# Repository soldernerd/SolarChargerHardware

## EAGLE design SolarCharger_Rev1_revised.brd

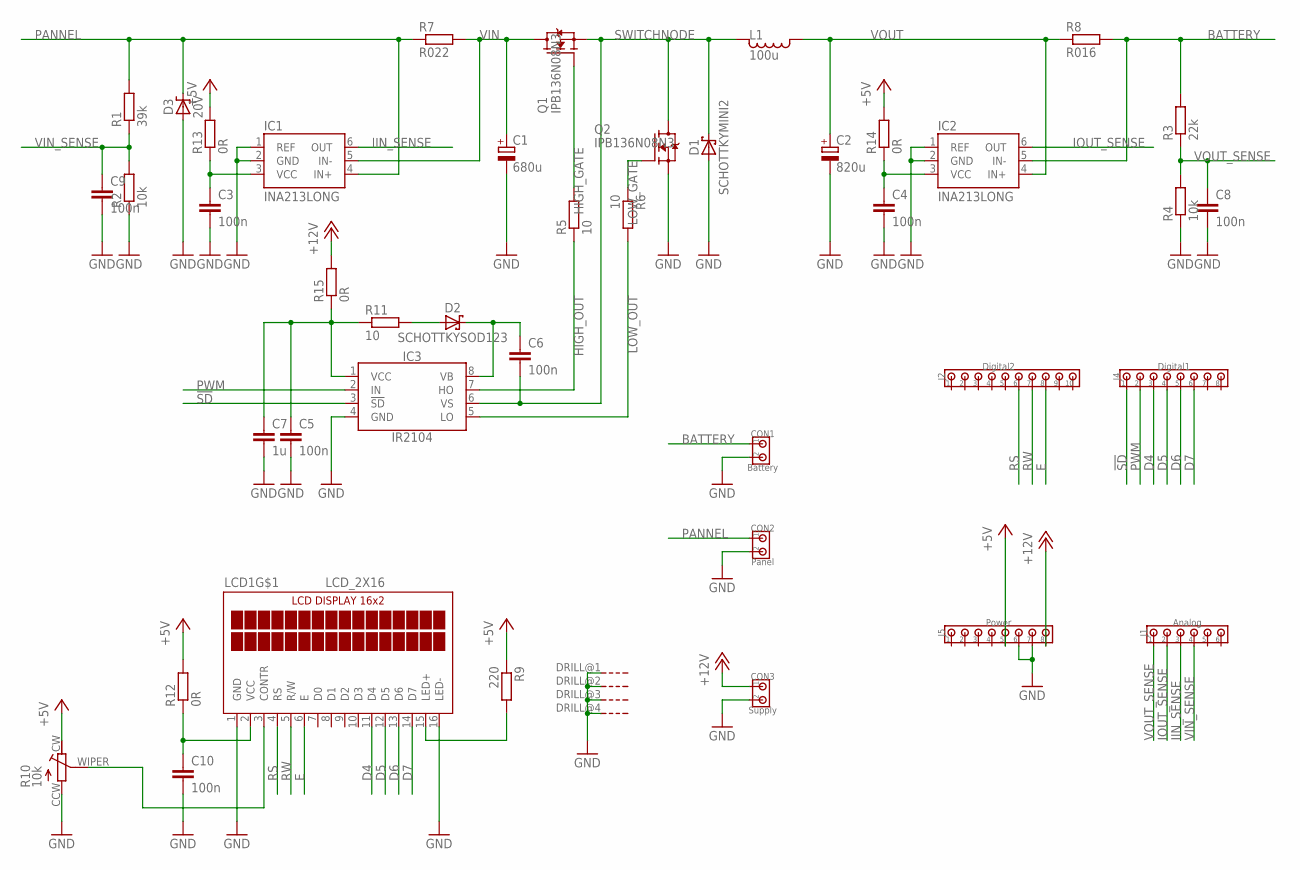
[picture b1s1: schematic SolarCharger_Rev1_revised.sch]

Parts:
C1: 680u; 10MM
C2: 820u; 10MM
C3, C4, C5, C6, C8, C9, C10: 100n; C0805
C7: 1u; C0805
CON1: Battery; 200MIL_2X
CON2: Panel; 200MIL_2X
CON3: Supply; 200MIL_2X
D1: SCHOTTKYMINI2; MINI2-F3-B
D2: SCHOTTKYSOD123; SOD123
D3: 20V; SMC
IC1, IC2: INA213LONG; SC70-6_LONG
IC3: IR2104; SOIC8
J1: Analog; 100MIL_6X_ROUND
J2: Digital2; 100MIL_10X_ROUND
J4: Digital1; 100MIL_8X_ROUND
J5: Power; 100MIL_8X_ROUND
L1: 100u; MSS1583
LCD1: LCD_2X16
Q1: IPB136N08N3; TO263-3
Q2: IPB136N08N3; TO263-3@1
R1: 39k; R0805
R2, R4: 10k; R0805
R3: 22k; R0805
R5, R6, R11: 10; R0805
R7: R022; 0612
R8: R016; 0612
R9: 220; R0805
R10: 10k; RTRIM3314G
R12, R13, R14, R15: 0R; R0805

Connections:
!SD!: IC3.3 (!SD!), J4.1
+5V: J5.5, R9.1, R10.CW, R12.2, R13.2, R14.2
+12V: CON3.1, J5.8, R15.2
BATTERY: CON1.1, IC2.5 (IN-), R3.2, R8.2
BOOT: C6.1, D2.C, IC3.8 (VB)
D4: J4.3, LCD1.11 (D4)
D5: J4.4, LCD1.12 (D5)
D6: J4.5, LCD1.13 (D6)
D7: J4.6, LCD1.14 (D7)
E: J2.8, LCD1.6 (E)
GND: C1.-, C2.-, C3.2, C4.2, C5.2, C7.2, C8.2, C9.2, C10.2, CON1.2, CON2.2, CON3.2, D1.A, D3.A, IC1.1 (REF), IC1.2 (GND), IC2.1 (REF), IC2.2 (GND), IC3.4 (GND), J5.6, J5.7, LCD1.1 (GND), LCD1.16 (LED-), LCD1.DRILL@1 (G), LCD1.DRILL@2 (G), LCD1.DRILL@3 (G), LCD1.DRILL@4 (G), Q2.3 (S), R2.1, R4.1, R10.CCW
HIGH_GATE: Q1.1 (G), R5.2
HIGH_OUT: IC3.7 (HO), R5.1
IIN_SENSE: IC1.6 (OUT), J1.3
IOUT_SENSE: IC2.6 (OUT), J1.2
LOW_GATE: Q2.1 (G), R6.1
LOW_OUT: IC3.5 (LO), R6.2
unnamed: C10.1, LCD1.2 (VCC), R12.1
unnamed: C3.1, IC1.3 (VCC), R13.1
unnamed: C4.1, IC2.3 (VCC), R14.1
unnamed: C5.1, C7.1, IC3.1 (VCC), R11.1, R15.1
unnamed: LCD1.15 (LED+), R9.2
unnamed: LCD1.3 (CONTR), R10.WIPER
unnamed: D2.A, R11.2
PANNEL: CON2.1, D3.C, IC1.4 (IN+), R1.2, R7.1
PWM: IC3.2 (IN), J4.2
RS: J2.6, LCD1.4 (RS)
RW: J2.7, LCD1.5 (R/W)
SWITCHNODE: C6.2, D1.C, IC3.6 (VS), L1.2, Q1.3 (S), Q2.TAB (D)
VIN: C1.+, IC1.5 (IN-), Q1.TAB (D), R7.2
VIN_SENSE: C9.1, J1.4, R1.1, R2.2
VOUT: C2.+, IC2.4 (IN+), L1.1, R8.1
VOUT_SENSE: C8.1, J1.1, R3.1, R4.2

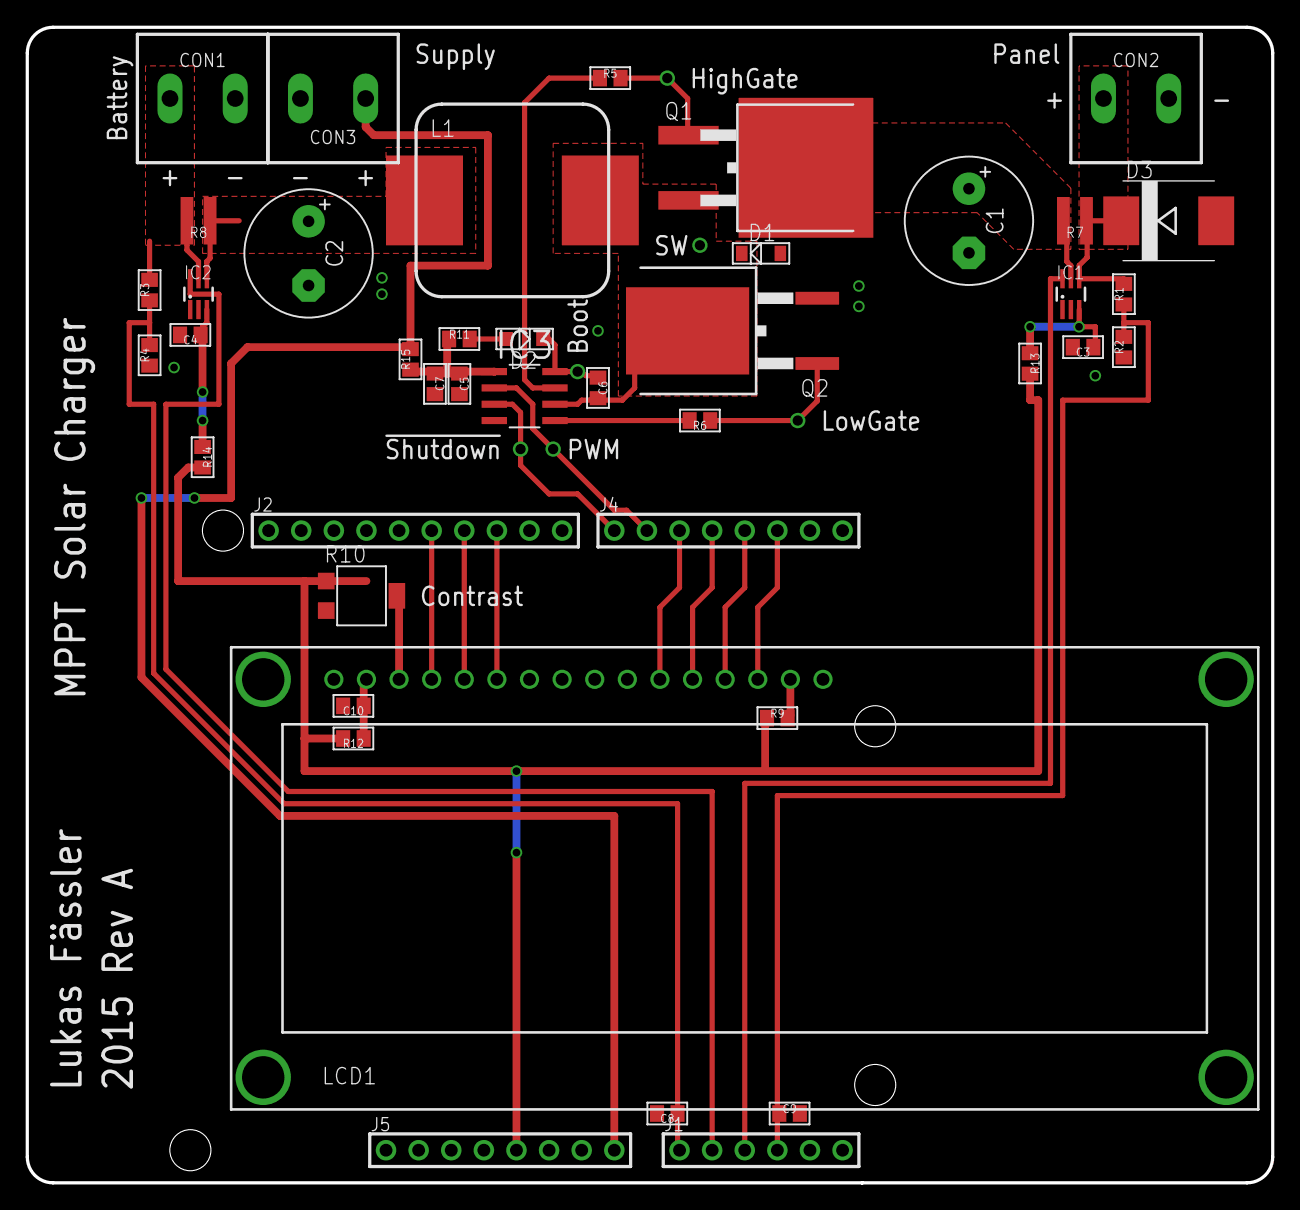
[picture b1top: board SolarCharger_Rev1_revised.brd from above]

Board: 2 copper layers, 97.0 x 90.0 mm, 42 parts (0 on the bottom side), 33 nets.

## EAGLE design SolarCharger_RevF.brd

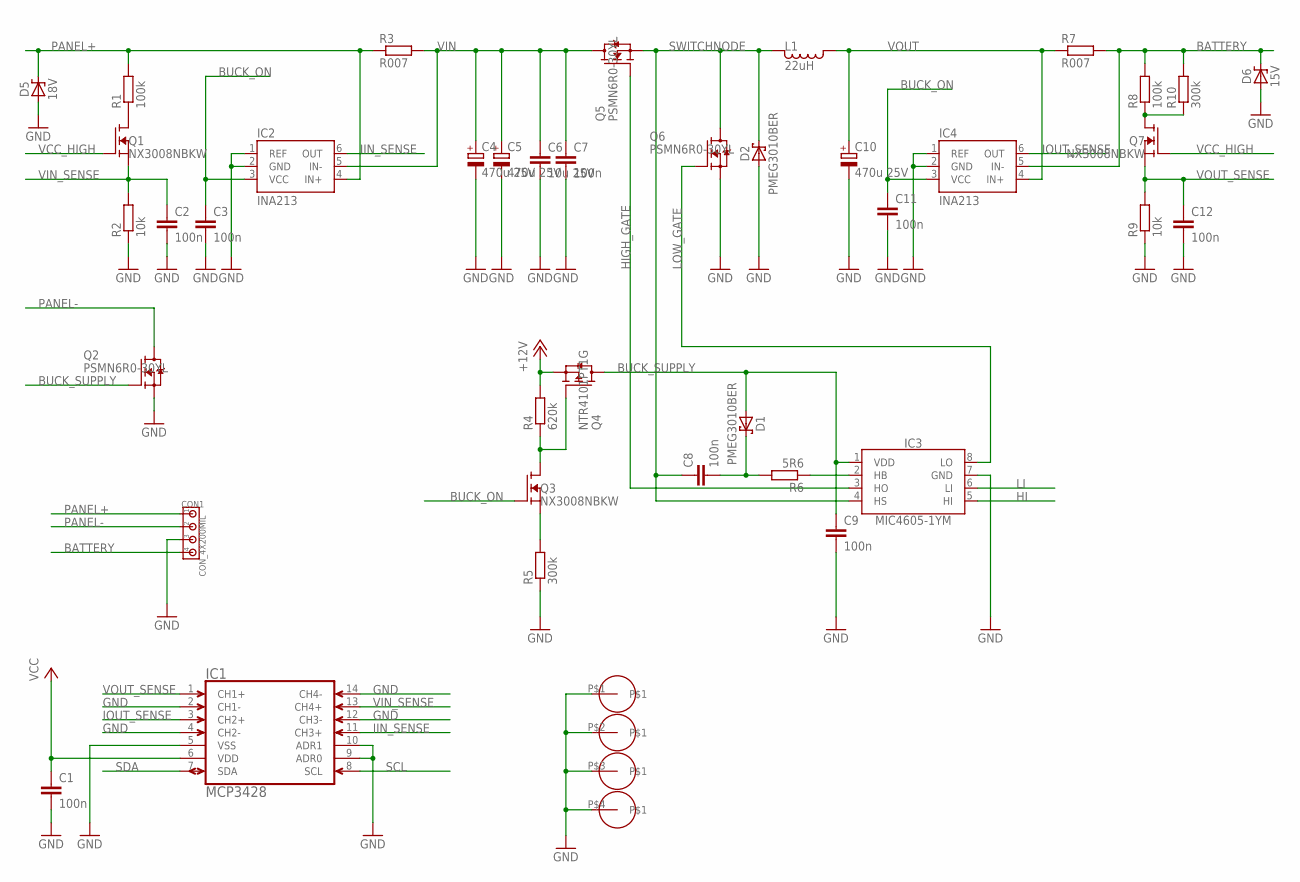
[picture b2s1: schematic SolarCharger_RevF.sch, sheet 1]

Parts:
C1, C2, C3, C7, C8, C9, C11, C12: 100n; C0805
C4, C5, C10: 470u 25V; 10MM
C6: 10u 25V; C1206
CON1: CON_4X200MIL; 200MIL_4X
D1, D2: PMEG3010BER; SOD123
D5: 18V; DO214AC
D6: 15V; DO214AC
DRL1: PCB_115_90
IC1: MCP3428; SO14
IC2, IC4: INA213; SC70-6
IC3: MIC4605-1YM; SOIC8
L1: 22uH; MSS1210
Q1, Q3, Q7: NX3008NBKW; SOT23
Q2, Q5, Q6: PSMN6R0-30YL; LFPAK
Q4: NTR4101PT1G; SOT23
R1, R8: 100k; R0805
R2, R9: 10k; R0805
R3, R7: R007; R1206
R4: 620k; R0805
R5, R10: 300k; R0805
R6: 5R6; R0805

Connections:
BATTERY: CON1.4, D6.C, IC4.5 (IN-), R7.2, R8.2, R10.2; also elsewhere on the board
BUCK_ON: C3.1, C11.1, IC2.3 (VCC), IC4.3 (VCC), Q3.1 (G); also elsewhere on the board
BUCK_SUPPLY: C9.1, D1.A, IC3.1 (VDD), Q2.4 (G), Q4.3 (D)
GND: C1.2, C2.2, C3.2, C4.-, C5.-, C6.2, C7.2, C9.2, C10.-, C11.2, C12.2, CON1.3, D2.A, D5.A, D6.A, DRL1.P$1, DRL1.P$2, DRL1.P$3, DRL1.P$4, IC1.2 (CH1-), IC1.4 (CH2-), IC1.5 (VSS), IC1.9 (ADR0), IC1.10 (ADR1), IC1.12 (CH3-), IC1.14 (CH4-), IC2.1 (REF), IC2.2 (GND), IC3.7 (GND), IC4.1 (REF), IC4.2 (GND), Q2.1 (S), Q2.2 (S), Q2.3 (S), Q6.1 (S), Q6.2 (S), Q6.3 (S), R2.1, R5.1, R9.1; also elsewhere on the board
HI: IC3.5 (HI); also elsewhere on the board
HIGH_GATE: IC3.3 (HO), Q5.4 (G)
IIN_SENSE: IC1.11 (CH3+), IC2.6 (OUT)
IOUT_SENSE: IC1.3 (CH2+), IC4.6 (OUT)
LI: IC3.6 (LI); also elsewhere on the board
LOW_GATE: IC3.8 (LO), Q6.4 (G)
unnamed: C8.2, D1.C, R6.2
unnamed: Q1.3 (D), R1.1
unnamed: IC3.2 (HB), R6.1
unnamed: Q3.3 (D), Q4.1 (G), R4.1
unnamed: Q7.3 (D), R8.1, R10.1
unnamed: Q3.2 (S), R5.2
PANEL+: CON1.1, D5.C, IC2.4 (IN+), R1.2, R3.1
PANEL-: CON1.2, Q2.MB1 (D), Q2.MB2 (D), Q2.MB3 (D), Q2.VIA1 (D), Q2.VIA2 (D), Q2.VIA3 (D), Q2.VIA4 (D), Q2.VIA5 (D), Q2.VIA6 (D), Q2.VIA7 (D), Q2.VIA8 (D), Q2.VIA9 (D)
SCL: IC1.8 (SCL); also elsewhere on the board
SDA: IC1.7 (SDA); also elsewhere on the board
SWITCHNODE: C8.1, D2.C, IC3.4 (HS), L1.2, L1.2B (2), L1.2C (2), L1.2D (2), L1.2E (2), L1.2F (2), L1.2G (2), L1.2H (2), Q5.1 (S), Q5.2 (S), Q5.3 (S), Q6.MB1 (D), Q6.MB2 (D), Q6.MB3 (D), Q6.VIA1 (D), Q6.VIA2 (D), Q6.VIA3 (D), Q6.VIA4 (D), Q6.VIA5 (D), Q6.VIA6 (D), Q6.VIA7 (D), Q6.VIA8 (D), Q6.VIA9 (D)
VCC: C1.1, IC1.6 (VDD); also elsewhere on the board
VCC_HIGH: Q1.1 (G), Q7.1 (G); also elsewhere on the board
VIN: C4.+, C5.+, C6.1, C7.1, IC2.5 (IN-), Q5.MB1 (D), Q5.MB2 (D), Q5.MB3 (D), Q5.VIA1 (D), Q5.VIA2 (D), Q5.VIA3 (D), Q5.VIA4 (D), Q5.VIA5 (D), Q5.VIA6 (D), Q5.VIA7 (D), Q5.VIA8 (D), Q5.VIA9 (D), R3.2
VIN_SENSE: C2.1, IC1.13 (CH4+), Q1.2 (S), R2.2
VOUT: C10.+, IC4.4 (IN+), L1.1, L1.1B (1), L1.1C (1), L1.1D (1), L1.1E (1), L1.1F (1), L1.1G (1), L1.1H (1), Q4.2 (S), R4.2, R7.1; also elsewhere on the board
VOUT_SENSE: C12.1, IC1.1 (CH1+), Q7.2 (S), R9.2

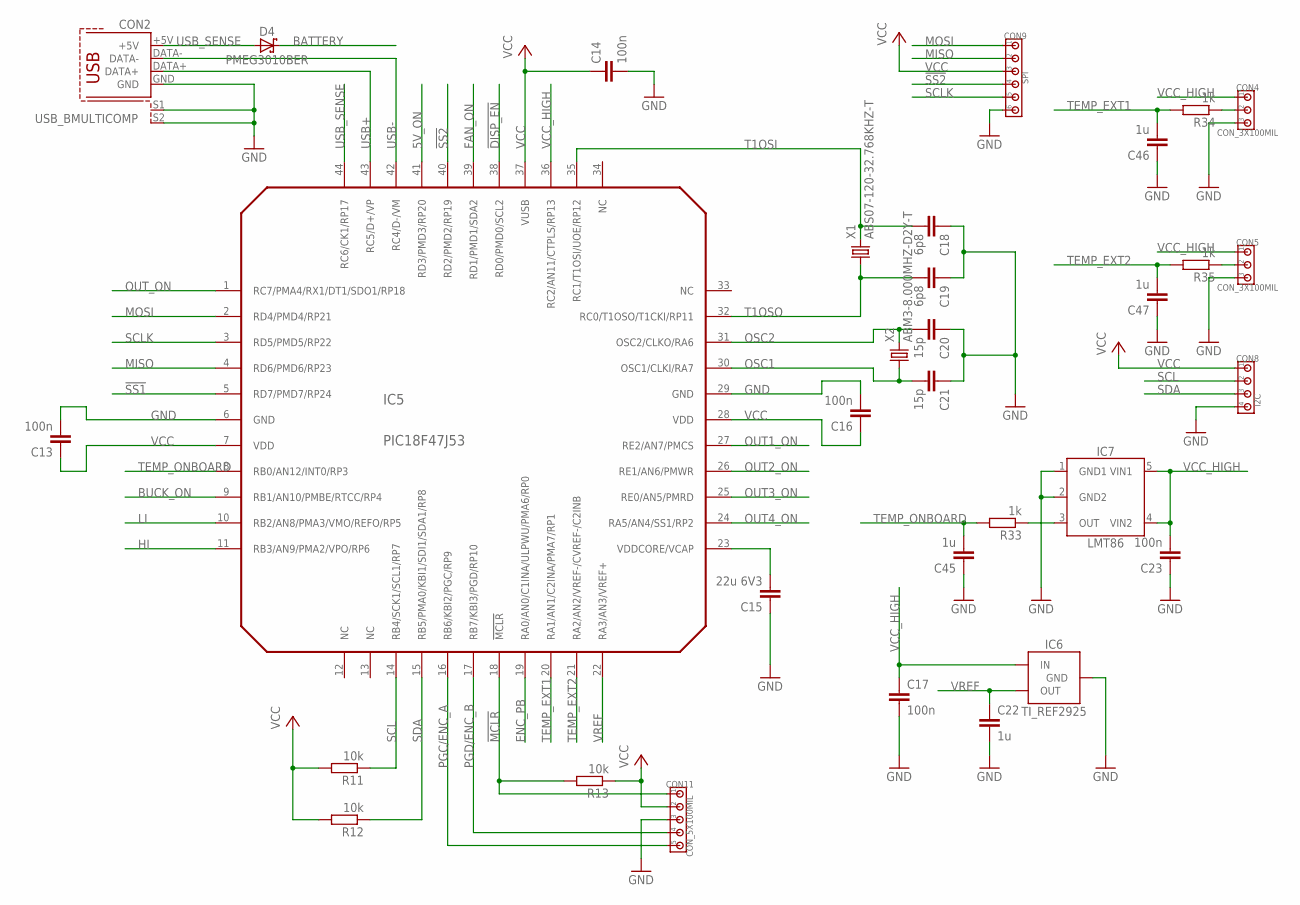
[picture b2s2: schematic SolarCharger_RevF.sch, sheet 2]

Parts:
C13, C14, C16, C17, C23: 100n; C0805
C15: 22u 6V3; C1206
C18, C19: 6p8; C0805
C20, C21: 15p; C0805
C22, C45, C46, C47: 1u; C0805
CON2: USB_BMULTICOMP; USB_B
CON4, CON5: CON_3X100MIL; 100MIL_3X
CON8: I2C; 100MIL_4X
CON9: SPI; 100MIL_3X2
CON11: CON_5X100MIL; 100MIL_5X
D4: PMEG3010BER; SOD123
IC5: PIC18F47J53; TQFP44
IC6: TI_REF2925; SOT23
IC7: LMT86; SC70-5
R11, R12, R13: 10k; R0805
R33, R34, R35: 1k; R0805
X1: ABS07-120-32.768KHZ-T; 3.2X1.5MM
X2: ABM3-8.000MHZ-D2Y-T; 5X3.2MM

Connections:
5V_ON: IC5.41 (RD3/PMD3/RP20); also elsewhere on the board
!DISP_EN!: IC5.38 (RD0/PMD0/SCL2); also elsewhere on the board
!MCLR!: CON11.1, IC5.18 (!MCLR!), R13.2
!SS1!: IC5.5 (RD7/PMD7/RP24); also elsewhere on the board
!SS2!: CON9.4, IC5.40 (RD2/PMD2/RP19)
BATTERY: D4.C; also elsewhere on the board
BUCK_ON: IC5.9 (RB1/AN10/PMBE/RTCC/RP4); also elsewhere on the board
ENC_PB: IC5.19 (RA0/AN0/C1INA/ULPWU/PMA6/RP0); also elsewhere on the board
FAN_ON: IC5.39 (RD1/PMD1/SDA2); also elsewhere on the board
GND: C13.2, C14.2, C15.1, C16.2, C17.2, C18.1, C19.1, C20.1, C21.1, C22.2, C23.1, C45.1, C46.1, C47.1, CON2.GND, CON2.S1, CON2.S2, CON4.3, CON5.3, CON8.4, CON9.6, CON11.3, IC5.6 (GND), IC5.29 (GND), IC6.3 (GND), IC7.1 (GND1), IC7.2 (GND2); also elsewhere on the board
HI: IC5.11 (RB3/AN9/PMA2/VPO/RP6); also elsewhere on the board
LI: IC5.10 (RB2/AN8/PMA3/VMO/REFO/RP5); also elsewhere on the board
MISO: CON9.2, IC5.4 (RD6/PMD6/RP23); also elsewhere on the board
MOSI: CON9.1, IC5.2 (RD4/PMD4/RP21); also elsewhere on the board
unnamed: C15.2, IC5.23 (VDDCORE/VCAP)
unnamed: IC7.3 (OUT), R33.1
unnamed: CON4.2, R34.1
unnamed: CON5.2, R35.1
OSC1: C21.2, IC5.30 (OSC1/CLKI/RA7), X2.1
OSC2: C20.2, IC5.31 (OSC2/CLKO/RA6), X2.2
OUT1_ON: IC5.27 (RE2/AN7/PMCS); also elsewhere on the board
OUT2_ON: IC5.26 (RE1/AN6/PMWR); also elsewhere on the board
OUT3_ON: IC5.25 (RE0/AN5/PMRD); also elsewhere on the board
OUT4_ON: IC5.24 (RA5/AN4/SS1/RP2); also elsewhere on the board
OUT_ON: IC5.1 (RC7/PMA4/RX1/DT1/SDO1/RP18); also elsewhere on the board
PGC/ENC_A: CON11.5, IC5.16 (RB6/KBI2/PGC/RP9); also elsewhere on the board
PGD/ENC_B: CON11.4, IC5.17 (RB7/KBI3/PGD/RP10); also elsewhere on the board
SCL: CON8.2, IC5.14 (RB4/SCK1/SCL1/RP7), R11.1; also elsewhere on the board
SCLK: CON9.5, IC5.3 (RD5/PMD5/RP22); also elsewhere on the board
SDA: CON8.3, IC5.15 (RB5/PMA0/KBI1/SDI1/SDA1/RP8), R12.1; also elsewhere on the board
T1OSI: C18.2, IC5.35 (RC1/T1OSI/UOE/RP12), X1.2
T1OSO: C19.2, IC5.32 (RC0/T1OSO/T1CKI/RP11), X1.1
TEMP_EXT1: C46.2, IC5.20 (RA1/AN1/C2INA/PMA7/RP1), R34.2
TEMP_EXT2: C47.2, IC5.21 (RA2/AN2/VREF-/CVREF-/C2INB), R35.2
TEMP_ONBOARD: C45.2, IC5.8 (RB0/AN12/INT0/RP3), R33.2
USB+: CON2.DATA+, IC5.43 (RC5/D+/VP)
USB-: CON2.DATA-, IC5.42 (RC4/D-/VM)
USB_SENSE: CON2.+5V, D4.A, IC5.44 (RC6/CK1/RP17)
VCC: C13.1, C14.1, C16.1, CON8.1, CON9.3, CON11.2, IC5.7 (VDD), IC5.28 (VDD), IC5.37 (VUSB), R11.2, R12.2, R13.1; also elsewhere on the board
VCC_HIGH: C17.1, C23.2, CON4.1, CON5.1, IC5.36 (RC2/AN11/CTPLS/RP13), IC6.1 (IN), IC7.4 (VIN2), IC7.5 (VIN1); also elsewhere on the board
VREF: C22.1, IC5.22 (RA3/AN3/VREF+), IC6.2 (OUT)

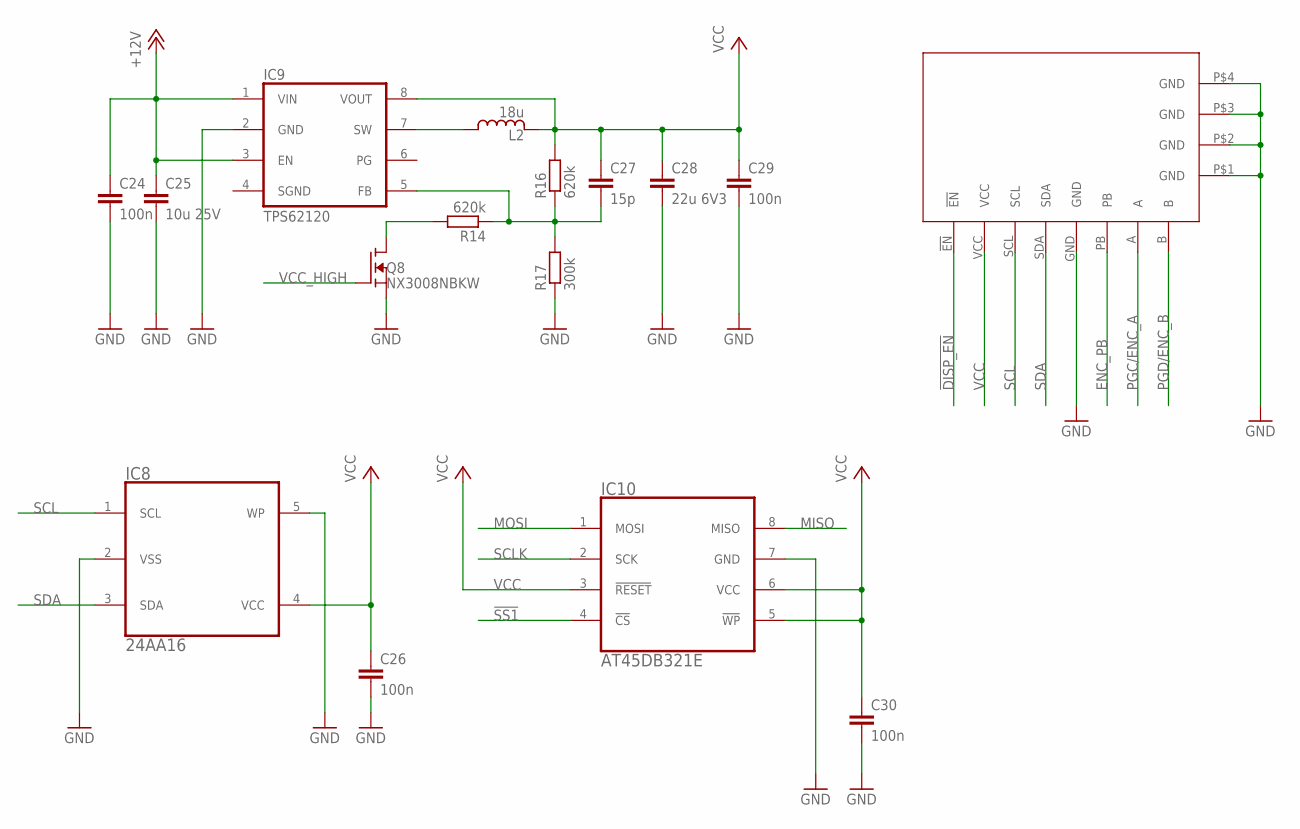
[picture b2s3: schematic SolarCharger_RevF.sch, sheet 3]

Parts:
BRD1: DISPLAY_UNIT
C24, C26, C29, C30: 100n; C0805
C25: 10u 25V; C1206
C27: 15p; C0805
C28: 22u 6V3; C1206
IC8: 24AA16; SOT-23-5
IC9: TPS62120; SOT-23-8
IC10: AT45DB321E; EIAJ_SOIC8
L2: 18u; LPS3015
Q8: NX3008NBKW; SOT23
R14, R16: 620k; R0805
R17: 300k; R0805

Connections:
!DISP_EN!: BRD1.!EN!; also elsewhere on the board
!SS1!: IC10.4 (!CS!); also elsewhere on the board
ENC_PB: BRD1.PB; also elsewhere on the board
GND: BRD1.GND, BRD1.P$1 (GND), BRD1.P$2 (GND), BRD1.P$3 (GND), BRD1.P$4 (GND), C24.2, C25.2, C26.2, C28.2, C29.2, C30.2, IC8.2 (VSS), IC8.5 (WP), IC9.2 (GND), IC10.7 (GND), Q8.2 (S), R17.1; also elsewhere on the board
MISO: IC10.8 (MISO); also elsewhere on the board
MOSI: IC10.1 (MOSI); also elsewhere on the board
unnamed: Q8.3 (D), R14.2
unnamed: IC9.7 (SW), L2.1, L2.1B (1), L2.1C (1), L2.1D (1), L2.1E (1)
unnamed: C27.2, IC9.5 (FB), R14.1, R16.1, R17.2
PGC/ENC_A: BRD1.A; also elsewhere on the board
PGD/ENC_B: BRD1.B; also elsewhere on the board
SCL: BRD1.SCL, IC8.1 (SCL); also elsewhere on the board
SCLK: IC10.2 (SCK); also elsewhere on the board
SDA: BRD1.SDA, IC8.3 (SDA); also elsewhere on the board
VCC: BRD1.VCC, C26.1, C27.1, C28.1, C29.1, C30.1, IC8.4 (VCC), IC9.8 (VOUT), IC10.3 (!RESET!), IC10.5 (!WP!), IC10.6 (VCC), L2.2, L2.2B (2), L2.2C (2), L2.2D (2), L2.2E (2), R16.2; also elsewhere on the board
VCC_HIGH: Q8.1 (G); also elsewhere on the board
VOUT: C24.1, C25.1, IC9.1 (VIN), IC9.3 (EN); also elsewhere on the board

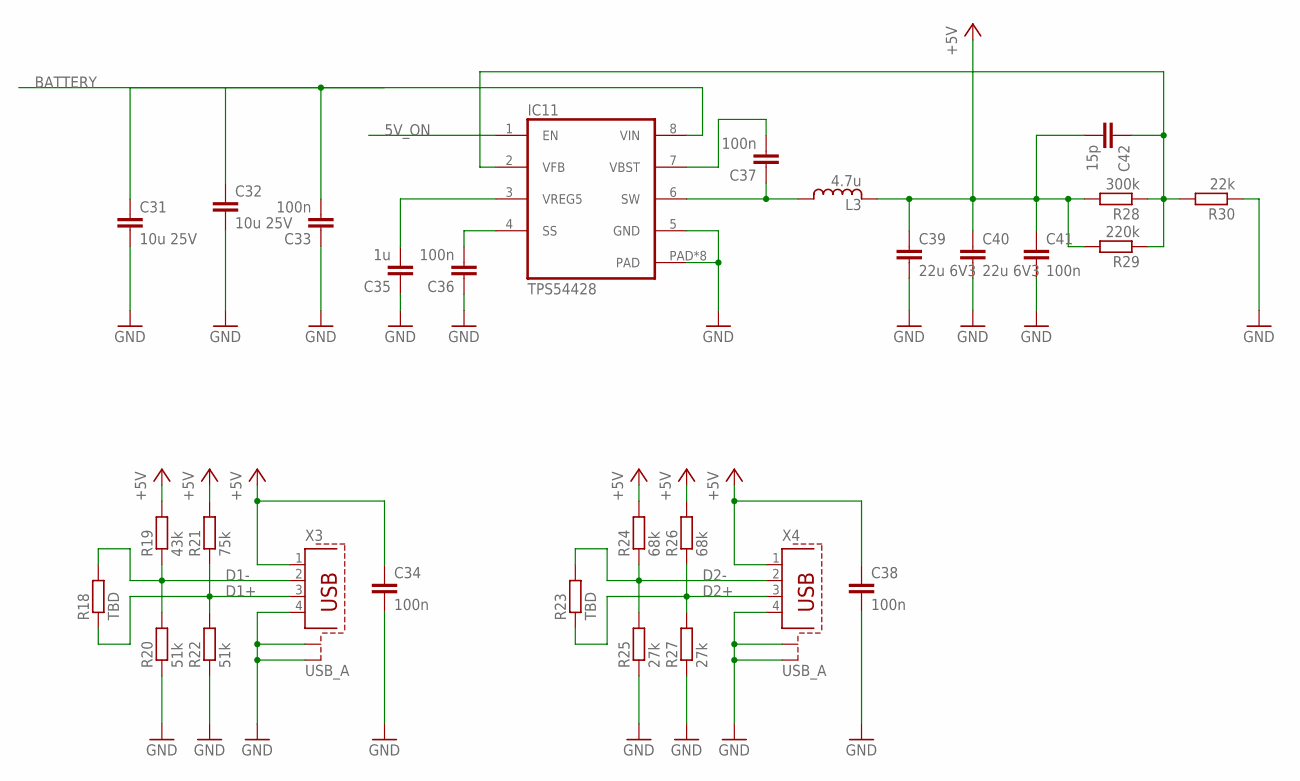
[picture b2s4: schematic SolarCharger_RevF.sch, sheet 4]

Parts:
C31, C32: 10u 25V; C1206
C33, C34, C36, C37, C38, C41: 100n; C0805
C35: 1u; C0805
C39, C40: 22u 6V3; C1206
C42: 15p; C0805
IC11: TPS54428; SOIC8_PWRPAD
L3: 4.7u; MSS1038
R18, R23: TBD; R0805
R19: 43k; R0805
R20, R22: 51k; R0805
R21: 75k; R0805
R24, R26: 68k; R0805
R25, R27: 27k; R0805
R28: 300k; R0805
R29: 220k; R0805
R30: 22k; R0805
X3, X4: USB_A

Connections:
5V_ON: IC11.1 (EN); also elsewhere on the board
+5V: C34.1, C38.1, C39.1, C40.1, C41.1, C42.2, L3.2, L3.2B (2), L3.2C (2), L3.2D (2), L3.2E (2), R19.2, R21.2, R24.2, R26.2, R28.2, R29.2, X3.1, X4.1
BATTERY: C31.1, C32.1, C33.2, IC11.8 (VIN); also elsewhere on the board
D1+: R18.1, R21.1, R22.2, X3.3
D1-: R18.2, R19.1, R20.2, X3.2
D2+: R23.1, R26.1, R27.2, X4.3
D2-: R23.2, R24.1, R25.2, X4.2
GND: C31.2, C32.2, C33.1, C34.2, C35.1, C36.1, C38.2, C39.2, C40.2, C41.2, IC11.5 (GND), IC11.PAD, IC11.PAD_BOTTOM (PAD), IC11.VIA1 (PAD), IC11.VIA2 (PAD), IC11.VIA3 (PAD), IC11.VIA4 (PAD), IC11.VIA5 (PAD), IC11.VIA6 (PAD), R20.1, R22.1, R25.1, R27.1, R30.1, X3.4, X3.S1, X3.S2, X4.4, X4.S1, X4.S2; also elsewhere on the board
unnamed: C37.2, IC11.7 (VBST)
unnamed: C37.1, IC11.6 (SW), L3.1, L3.1B (1), L3.1C (1), L3.1D (1), L3.1E (1)
unnamed: C35.2, IC11.3 (VREG5)
unnamed: C36.2, IC11.4 (SS)
unnamed: C42.1, IC11.2 (VFB), R28.1, R29.1, R30.2

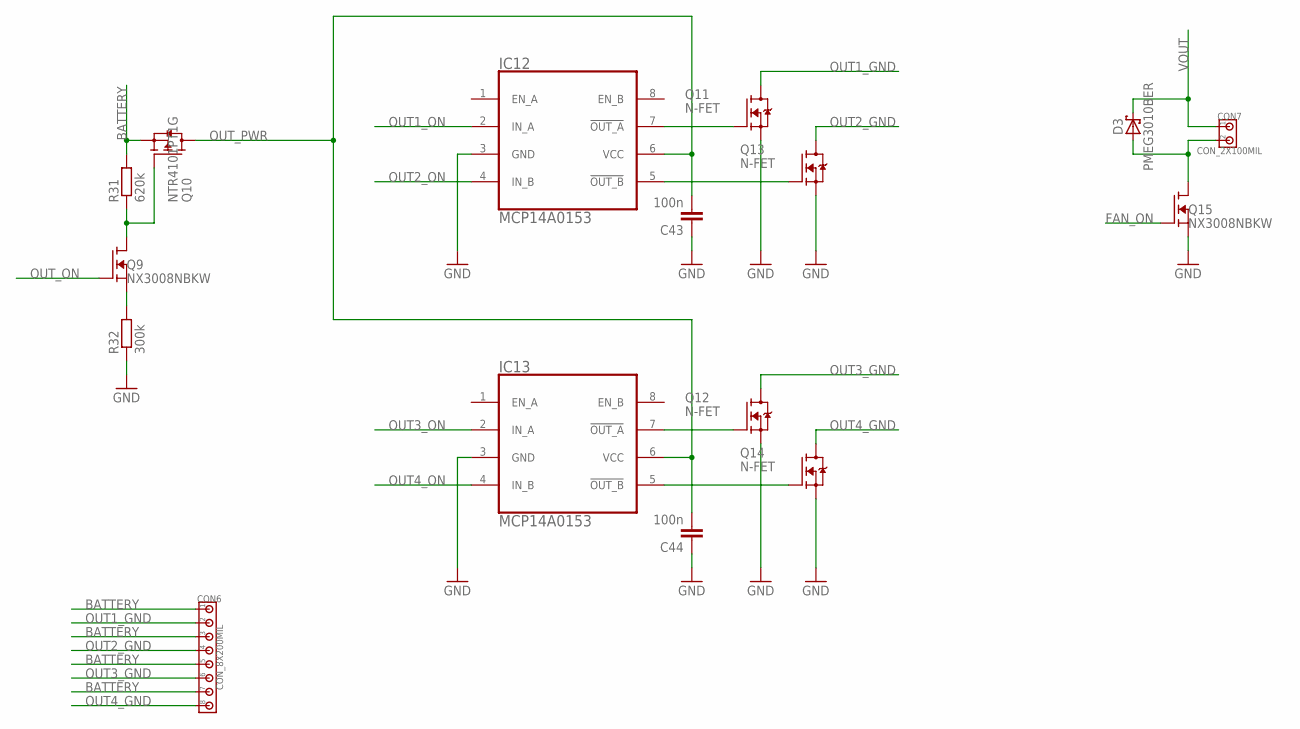
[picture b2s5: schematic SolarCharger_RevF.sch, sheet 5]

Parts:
C43, C44: 100n; C0805
CON6: CON_8X200MIL; 200MIL_8X
CON7: CON_2X100MIL; 100MIL_2X
D3: PMEG3010BER; SOD123
IC12, IC13: MCP14A0153; SSOP8
Q9, Q15: NX3008NBKW; SOT23
Q10: NTR4101PT1G; SOT23
Q11, Q12, Q13, Q14: N-FET; LFPAK
R31: 620k; R0805
R32: 300k; R0805

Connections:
BATTERY: CON6.1, CON6.3, CON6.5, CON6.7, Q10.2 (S), R31.2; also elsewhere on the board
FAN_ON: Q15.1 (G); also elsewhere on the board
GND: C43.1, C44.1, IC12.3 (GND), IC13.3 (GND), Q11.1 (S), Q11.2 (S), Q11.3 (S), Q12.1 (S), Q12.2 (S), Q12.3 (S), Q13.1 (S), Q13.2 (S), Q13.3 (S), Q14.1 (S), Q14.2 (S), Q14.3 (S), Q15.2 (S), R32.1; also elsewhere on the board
unnamed: Q9.3 (D), Q10.1 (G), R31.1
unnamed: CON7.2, D3.A, Q15.3 (D)
unnamed: IC12.7 (!OUT_A!), Q11.4 (G)
unnamed: IC13.5 (!OUT_B!), Q14.4 (G)
unnamed: IC13.7 (!OUT_A!), Q12.4 (G)
unnamed: IC12.5 (!OUT_B!), Q13.4 (G)
unnamed: Q9.2 (S), R32.2
OUT1_GND: CON6.2, Q11.MB1 (D), Q11.MB2 (D), Q11.MB3 (D), Q11.VIA1 (D), Q11.VIA2 (D), Q11.VIA3 (D), Q11.VIA4 (D), Q11.VIA5 (D), Q11.VIA6 (D), Q11.VIA7 (D), Q11.VIA8 (D), Q11.VIA9 (D)
OUT1_ON: IC12.2 (IN_A); also elsewhere on the board
OUT2_GND: CON6.4, Q13.MB1 (D), Q13.MB2 (D), Q13.MB3 (D), Q13.VIA1 (D), Q13.VIA2 (D), Q13.VIA3 (D), Q13.VIA4 (D), Q13.VIA5 (D), Q13.VIA6 (D), Q13.VIA7 (D), Q13.VIA8 (D), Q13.VIA9 (D)
OUT2_ON: IC12.4 (IN_B); also elsewhere on the board
OUT3_GND: CON6.6, Q12.MB1 (D), Q12.MB2 (D), Q12.MB3 (D), Q12.VIA1 (D), Q12.VIA2 (D), Q12.VIA3 (D), Q12.VIA4 (D), Q12.VIA5 (D), Q12.VIA6 (D), Q12.VIA7 (D), Q12.VIA8 (D), Q12.VIA9 (D)
OUT3_ON: IC13.2 (IN_A); also elsewhere on the board
OUT4_GND: CON6.8, Q14.MB1 (D), Q14.MB2 (D), Q14.MB3 (D), Q14.VIA1 (D), Q14.VIA2 (D), Q14.VIA3 (D), Q14.VIA4 (D), Q14.VIA5 (D), Q14.VIA6 (D), Q14.VIA7 (D), Q14.VIA8 (D), Q14.VIA9 (D)
OUT4_ON: IC13.4 (IN_B); also elsewhere on the board
OUT_ON: Q9.1 (G); also elsewhere on the board
OUT_PWR: C43.2, C44.2, IC12.6 (VCC), IC13.6 (VCC), Q10.3 (D)
VOUT: CON7.1, D3.C; also elsewhere on the board

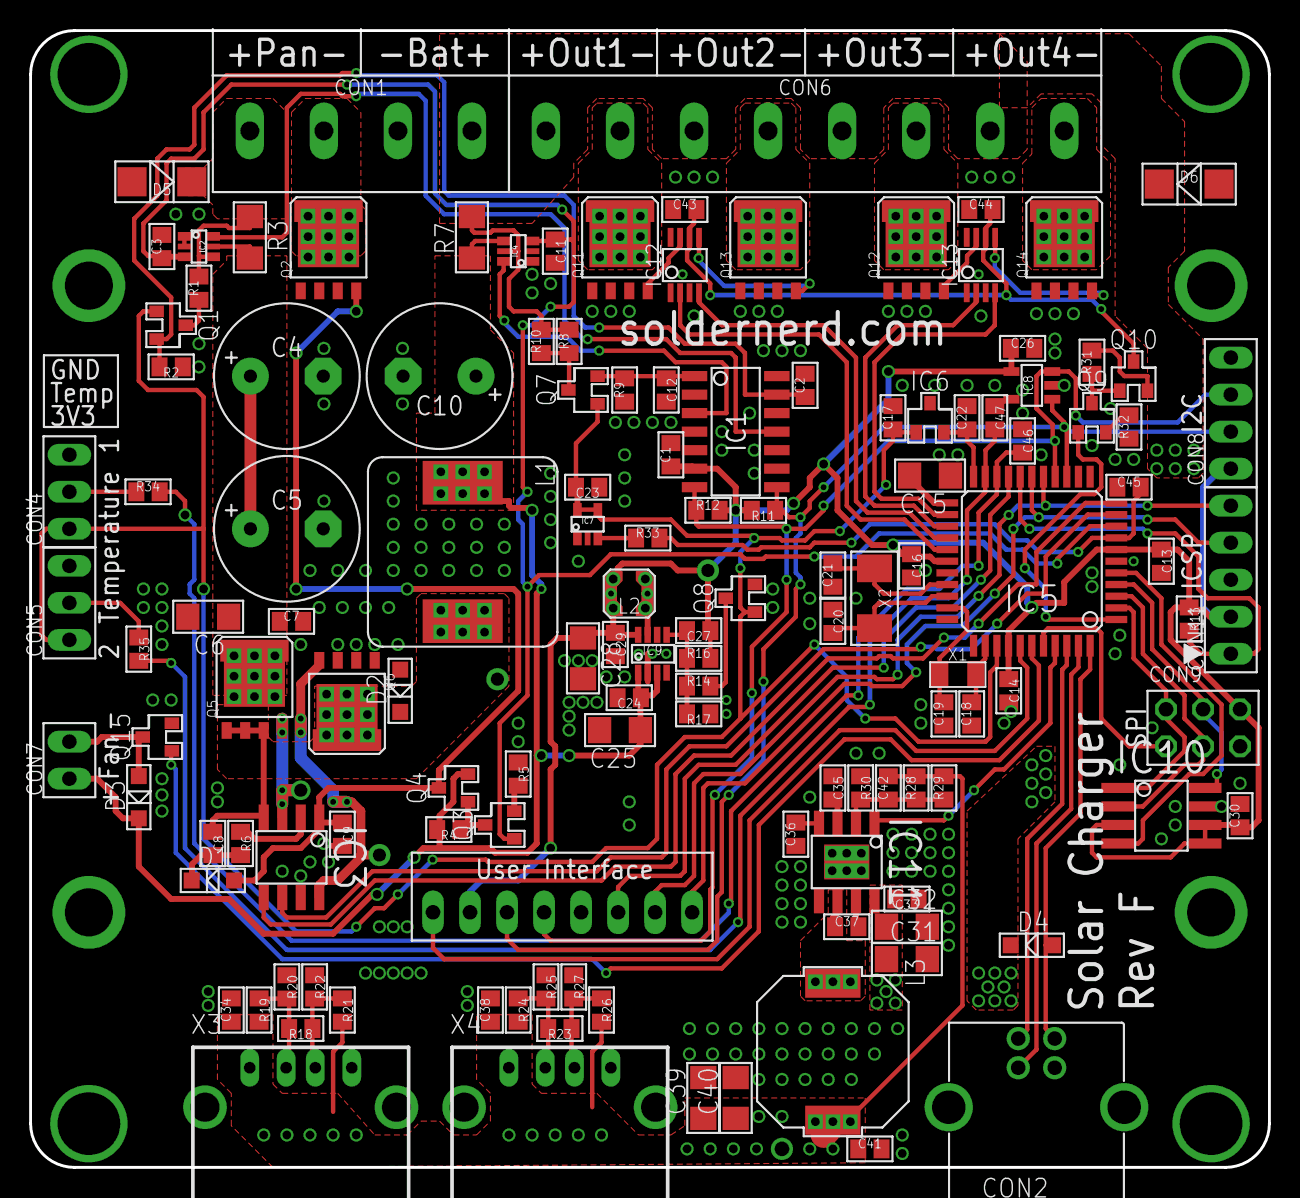
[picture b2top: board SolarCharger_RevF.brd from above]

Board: 2 copper layers, 85.0 x 78.0 mm, 133 parts (0 on the bottom side), 84 nets.

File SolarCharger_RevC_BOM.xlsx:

Quantity | Description | Value | Package | Manufacturer | Model | Marking | Farnell | Parts | Unit Price | Price | Price inkl MwSt
1 | Board | n/a | 78x85mm | soldernerd.com | Solar Charger Rev C | Solar Charger Rev C | n/a | n/a | 3 | 3 | 3.2608695652173911
4 | 3-pin-header | n/a | 200 mil | Weidmueller | PM5.08/3/90 | n/a | 1131854 | CON1, CON6 | 0.26 | 1.04 | 1.1304347826086956
1 | 6-pin header | ICSP | 100MIL_6X |  | CON_6X100MIL |  |  | CON3 | 0.5 | 0.5 | 0.54347826086956519
1 | Type B USB 2.0 Connector | n/a | USB B | Multicomp | USB-B-S-RA | n/a | 2112373 | CON2 | 0.6 | 0.6 | 0.65217391304347816
2 | Type A USB connector | n/a | USB_A | Multicomp | MC32593 | n/a | 1696534 | X3, X4 | 0.53200000000000003 | 1.0640000000000001 | 1.1565217391304348
1 | Low-power 8bit microcontroller with USB | PIC18F46J50 | TQFP44 | Microchip | PIC18F46J50 | PIC18F46J50 | 1706312 | IC5 | 3.4 | 3.4 | 3.695652173913043
1 | Crystal | 8MHz | 5mm x 3.2mm | Abracon | ABM3-8.000MHZ-D2Y-T | 080 | 2101329 | X2 | 0.7 | 0.7 | 0.76086956521739124
1 | Crystal | 32.768kHz | 3.2mm x 1.5mm | Abracon | ABS07-120-32.768KHZ-T |  | 2467864 | X1 | 0.76200000000000001 | 0.76200000000000001 | 0.82826086956521738
1 | EEPROM | 16Kbit | SOT23-5 | Microchip | 24AA16T-I/OT | B5xx | 1331290 | IC8 | 0.35 | 0.35 | 0.38043478260869562
1 | Serial Flash Memory with Uniform 4 kB Sectors | 8MBit | SOIC8 | Cypress Semiconductor | S25FL208K |  | 2340553 | IC10 | 1.1000000000000001 | 1.1000000000000001 | 1.1956521739130435
1 | 16-Bit, 4-Channel Analog-to-Digital Converter | n/a | SO14 | Microchip | MCP3428 |  | 1801128 | IC1 | 2.3199999999999998 | 2.3199999999999998 | 2.5217391304347823
1 | Voltage Reference | 2.5V | SOT23 | Silicon Labs | TS6001 |  | 2373823 | IC6 | 1.1000000000000001 | 1.1000000000000001 | 1.1956521739130435
1 | Analog Temperature Sensors with Class-AB Output | LMT86 | SC70-5 | Texas Instruments | LMT86 |  | 2314388 | IC7 | 0.55100000000000005 | 0.55100000000000005 | 0.59891304347826091
2 | Current-Shunt Monitors | Gain=50 | SC70-6 | Texas Instruments | INA213AIDCKT |  | 1754261 | IC2, IC4 | 1.35 | 2.7 | 2.9347826086956523
1 | 15V, 75mA, 800kHz High Efficient Buck Converter | TPS62120 | SOT-23-8 | Texas Instruments | TPS62120 |  | 1864820 | IC9 | 1.42 | 1.42 | 1.543478260869565
1 | Synchronous Step-Down Converter | TPS54428 | SOIC8_PWRPAD | Texas Instruments | TPS54428 |  | 2078519 | IC11 | 1.97 | 1.97 | 2.1413043478260869
2 | 1.5A Dual MOSFET Driver | n/a | SSOP8 | Microchip | MCP14A0153-E/MS |  | 2524543 | IC12, IC13 | 0.76 | 1.52 | 1.6521739130434783
1 | 85V Half-Bridge MOSFET Driver | n/a | SOIC8 | Microchip | MIC4605-1YM | MIC4605 | 2510168 | IC3 | 0.76700000000000002 | 0.76700000000000002 | 0.83369565217391306
2 | Resistor | 7mOhms 1% 1W | 1206, metric 3216 | TE Connectivity | TLR2B10DR007FTDG | n/a | 2332217 | R3, R7 | 0.9 | 1.8 | 1.9565217391304348
1 | Resistor | 5R6 | R0805 |  | RESISTORR0805 |  |  | R6 | 0.1 | 0.1 | 0.10869565217391304
5 | Resistor | 10kOhms | 0805, metric 2012 | Multicomp | MC01W0805110K | 1002 | 9332391 | R2, R9, R11, R12, R13 | 0.01 | 0.05 | 5.434782608695652E-2
1 | Resistor | 22k | R0805 | Multicomp | MC01W0805122K |  | 9332820 | R30 | 0.01 | 0.01 | 1.0869565217391304E-2
2 | Resistor | 27k | R0805 | Multicomp | MC01W0805127K |  | 9332952 | R25, R27 | 0.01 | 0.02 | 2.1739130434782608E-2
1 | Resistor | 43k | R0805 | Multicomp | MC01W0805143K |  | 9333223 | R19 | 0.01 | 0.01 | 1.0869565217391304E-2
2 | Resistor | 51k | R0805 | Multicomp | MC01W0805151K |  | 9333339 | R20, R22 | 0.01 | 0.02 | 2.1739130434782608E-2
2 | Resistor | 68k | R0805 | Multicomp | MC01W0805168K |  | 9333487 | R24, R26 | 0.01 | 0.02 | 2.1739130434782608E-2
1 | Resistor | 75k | R0805 | Multicomp | MC01W0805175K |  | 9333541 | R21 | 0.01 | 0.01 | 1.0869565217391304E-2
3 | Resistor | 100k | R0805 | Multicomp | MC01W08051100K |  | 9332405 | R1, R8, R15 | 0.01 | 0.03 | 3.2608695652173912E-2
1 | Resistor | 220k | R0805 | Multicomp | MC01W08051220K |  | 9332839 | R29 | 0.01 | 0.01 | 1.0869565217391304E-2
5 | Resistor | 300k | R0805 | Multicomp | MC01W08051300K |  | 9333010 | R5, R10, R17, R28, R32 | 0.01 | 0.05 | 5.434782608695652E-2
4 | Resistor | 620k | R0805 | Multicomp | MC01W08051620K |  | 9333444 | R4, R14, R16, R31 | 0.01 | 0.04 | 4.3478260869565216E-2
2 | Ceramic capacitor | 6p8 | 0805, metric 2012 |  | CC0805 |  |  | C18, C19 | 0.2 | 0.4 | 0.43478260869565216
4 | Ceramic capacitor | 15p | 0805, metric 2012 |  | CC0805 |  |  | C20, C21, C27, C42 | 0.2 | 0.8 | 0.86956521739130432
1 | Ceramic capacitor | 1.8n | 0805, metric 2012 |  | CC0805 |  |  | C22 | 0.2 | 0.2 | 0.21739130434782608
25 | Ceramic capacitor | 100nF, 50V, X7R | 0805, metric 2012 | Multicomp | MC0805B104K500CT | n/a | 1759265 | C1, C2, C3, C7, C8, C9, C11, C12, C13, C14, C16, C17, C23, C24, C26, C29, C30, 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 | 1.4999999999999999E-2 | 0.375 | 0.40760869565217389
1 | Ceramic capacitor | 1u 25V | 0805, metric 2012 | Murata | GRM219R71E105KA88D |  | 1845770 | C35 | 5.1999999999999998E-2 | 5.1999999999999998E-2 | 5.6521739130434775E-2
4 | Ceramic capacitor | 10uF, 6.3V, X7R | 0805, metric 2012 | Multicomp | MC0805B106K6R3CT | n/a | 2320851 | C6, C25, C31, C32 | 6.2E-2 | 0.248 | 0.26956521739130435
4 | Ceramic capacitor | 22u 6V3 | 1206, metric 3216 | TDK | C3216X5R0J226M085AC |  | 2526272 | C15, C28, C39, C40 | 0.16 | 0.64 | 0.69565217391304346
3 | Electrolytic capacitor | 470u 25V | 10mm x 12.5mm | Panasonic | EEUFR1E471B |  | 1800650 | C4, C5, C10 | 0.27 | 0.81 | 0.88043478260869568
1 | Inductor | 18u | 2.95mm x 2.95mm x 1.4mm | Coilcraft | LPS3015-183MRB |  | 2408026 | L2 | 0.95 | 0.95 | 1.0326086956521738
1 | Inductor | 4.7u | 10.2mm x 10.2mm x 4.8mm | Coilcraft | MSS1048-472NLC |  | 2288282 | L3 | 1.86 | 1.86 | 2.0217391304347827
1 | Inductor | 22uH | 12mm x 12mm | Coilcraft | MSS1210-223MED | 226 | 2288332 | L1 | 2.5 | 2.5 | 2.7173913043478262
3 | Schottky diode | n/a | SOD123-W | NXP | PMEG3010BER | n/a | 1907684 | D1, D2, D3 | 0.17 | 0.51 | 0.55434782608695654
6 | N-Channel MOSFET | n/a | SOT23 | NXP | NX3008NBKW |  | 2069546 | Q1, Q3, Q7, Q8, Q9, Q15 | 0.05 | 0.30000000000000004 | 0.32608695652173919
2 | P-channel MOSFET | n/a | SOT23 | On Semiconductor | NTR4101PT1G |  | 2124699 | Q4, Q10 | 0.14000000000000001 | 0.28000000000000003 | 0.30434782608695654
7 | N-Channel MOSFET | 30V | LFPAK / SOT669 | NXP | PSMN6R0-30YL |  | 1699709 | Q2, Q5, Q6, Q11, Q12, Q13, Q14 | 0.42499999999999999 | 2.9750000000000001 | 3.2336956521739131
 |  |  |  |  |  |  |  |  |  | 39.934000000000005 | 43.406521739130426
 |  |  |  |  |  |  |  |  |  |  | 45.215126811594196
 |  |  |  |  |  |  |  |  |  |  | 47.099090428743956
